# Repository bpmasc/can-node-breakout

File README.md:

# can-node-breakout

Version 0.0.1

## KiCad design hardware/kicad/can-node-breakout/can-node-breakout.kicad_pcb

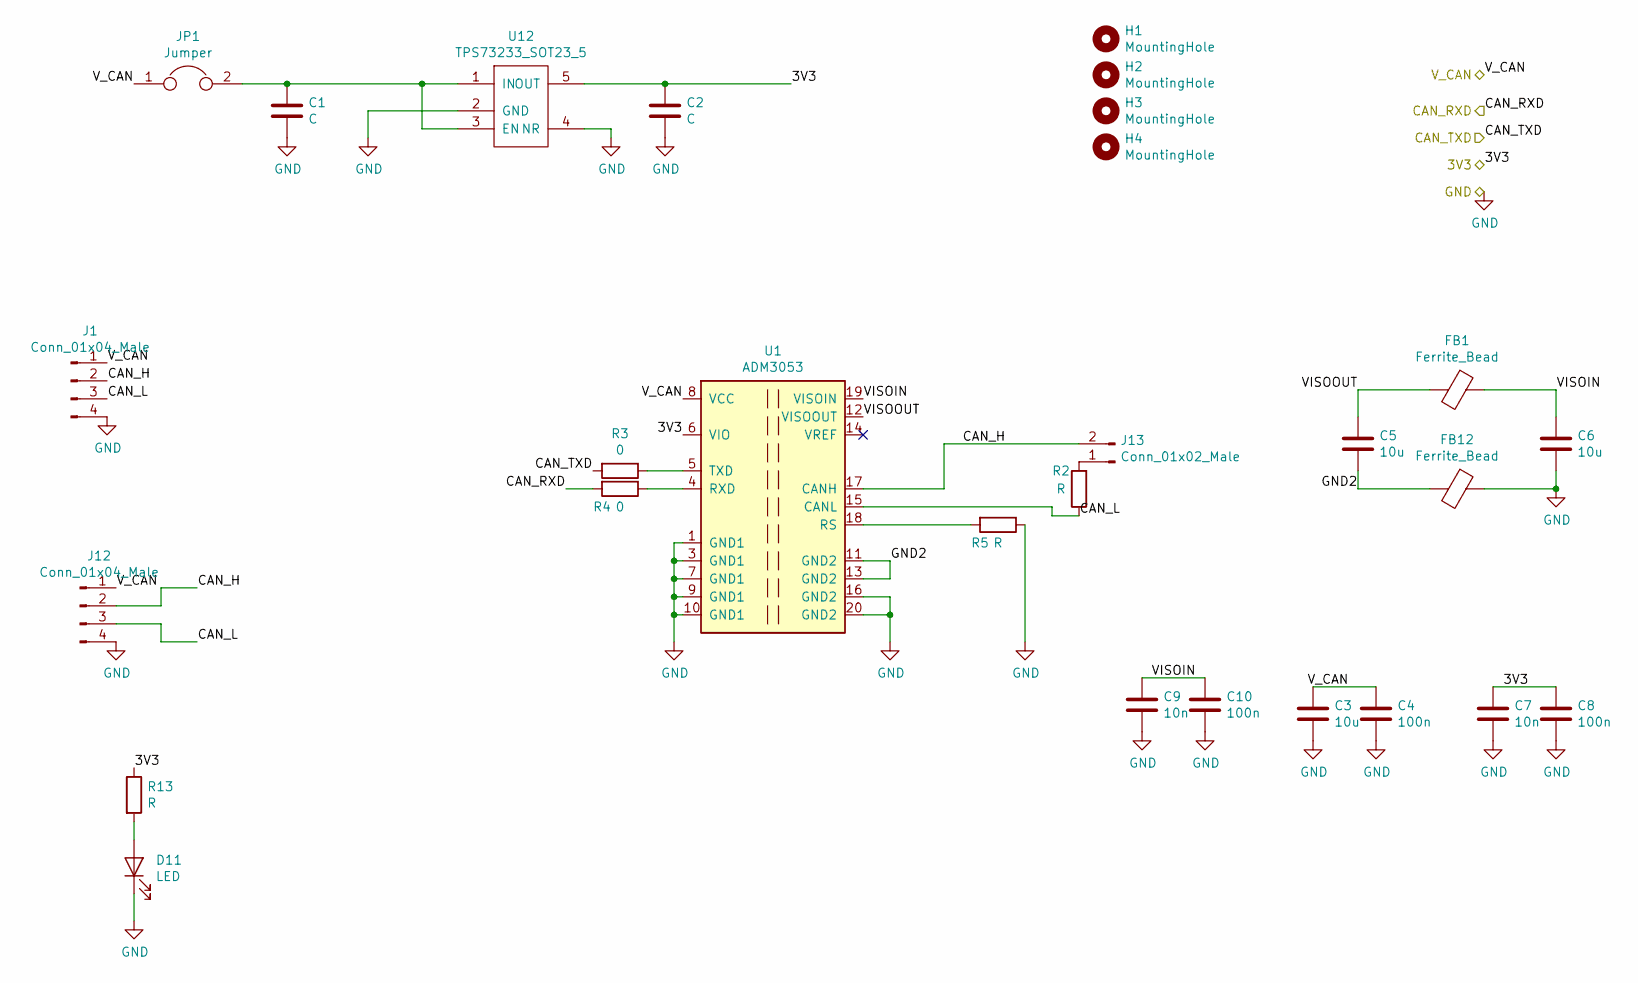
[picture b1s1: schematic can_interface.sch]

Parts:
C1, C2: C; C_0603
C3, C5, C6: 10u; C_0603
C4, C8, C10: 100n; C_0603
C7, C9: 10n; C_0603
D11: LED; LED_0603_1608Metric
FB1, FB12: Ferrite_Bead; L_0603
H1, H2, H3, H4: MountingHole; MountingHole_2.2mm_M2
J1, J12: Conn_01x04_Male; JST_GH_SM04B-GHS-TB_04x1.25mm_Angled
J13: Conn_01x02_Male; Pin_Header_Straight_1x02_Pitch2.54mm
JP1: Jumper; SolderJumper-2_P1.3mm_Open_Pad1.0x1.5mm
R2, R5, R13: R; R_0603_1608Metric
R3, R4: 0; R_0603_1608Metric
U1: ADM3053; SOIC-20W_7.5x12.8mm_Pitch1.27mm
U12: TPS73233_SOT23_5; SOT-23-5

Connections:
/can_interface/3V3: C2.1, C7.1, C8.1, R13.1, U1.6 (VIO), U12.5 (OUT); also elsewhere on the board
/can_interface/CAN_H: J1.2, J12.2, J13.2, U1.17 (CANH)
/can_interface/CAN_L: J1.3, J12.3, R2.1, U1.15 (CANL)
/can_interface/CAN_RXD: R4.2; also elsewhere on the board
/can_interface/CAN_TXD: R3.2; also elsewhere on the board
/can_interface/GND2: C5.2, FB12.2, U1.11 (GND2), U1.13 (GND2)
/can_interface/VISOIN: C6.1, C9.1, C10.1, FB1.1, U1.19 (VISOIN)
/can_interface/VISOOUT: C5.1, FB1.2, U1.12 (VISOOUT)
/can_interface/V_CAN: C3.1, C4.1, J1.1, J12.1, JP1.1, U1.8 (VCC); also elsewhere on the board
GND: C1.2, C2.2, C3.2, C4.2, C6.2, C7.2, C8.2, C9.2, C10.2, D11.1 (K), FB12.1, J1.4, J12.4, R5.1, U1.1 (GND1), U1.3 (GND1), U1.7 (GND1), U1.9 (GND1), U1.10 (GND1), U1.16 (GND2), U1.20 (GND2), U12.2 (GND), U12.4 (NR); also elsewhere on the board
unnamed: C1.1, JP1.2, U12.1 (IN), U12.3 (EN)
unnamed: D11.2 (A), R13.2
unnamed: J13.1, R2.2
unnamed: R3.1, U1.5 (TXD)
unnamed: R4.1, U1.4 (RXD)
unnamed: R5.2, U1.18 (RS)

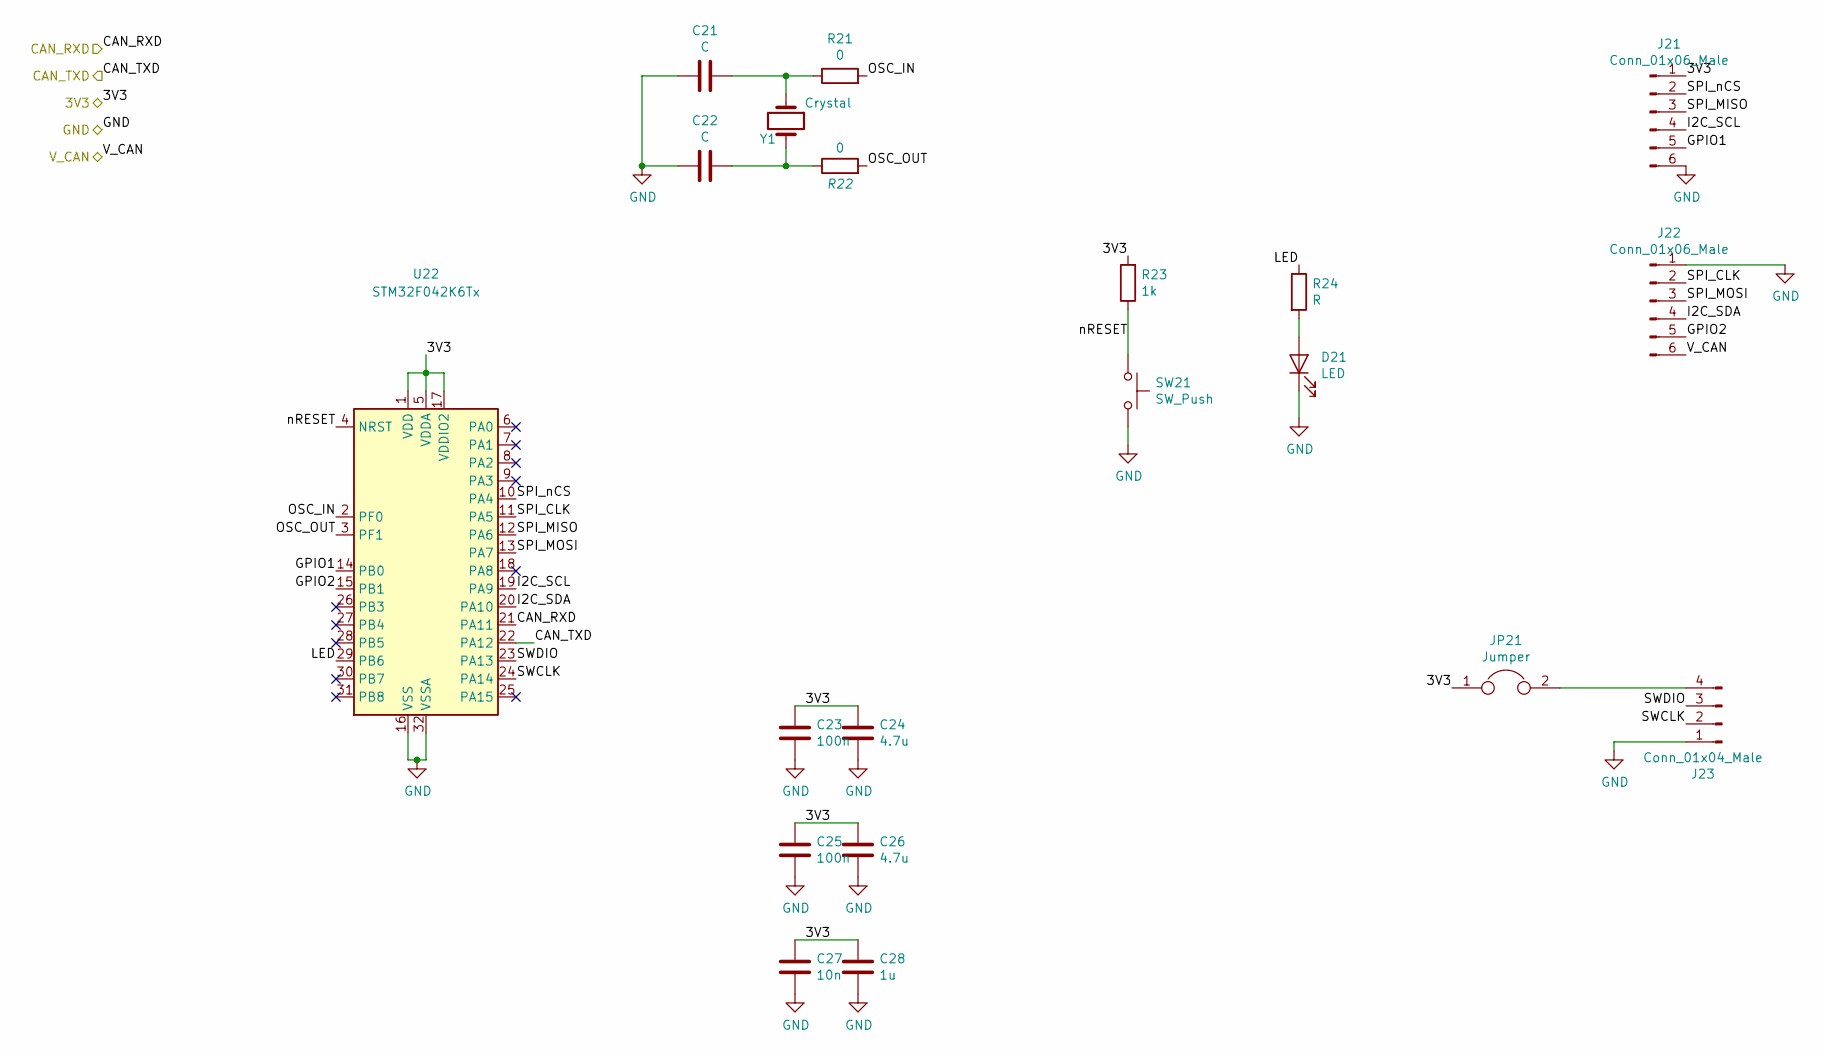
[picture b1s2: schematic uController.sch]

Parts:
C21, C22: C; C_0603
C23, C25: 100n; C_0603
C24, C26: 4.7u; C_0603
C27: 10n; C_0603
C28: 1u; C_0603
D21: LED; LED_0603_1608Metric
J21, J22: Conn_01x06_Male; Pin_Header_Straight_1x06_Pitch2.54mm
J23: Conn_01x04_Male; Pin_Header_Straight_1x04_Pitch2.54mm
JP21: Jumper; SolderJumper-2_P1.3mm_Open_Pad1.0x1.5mm
R21, R22: 0; R_0603_1608Metric
R23: 1k; R_0603_1608Metric
R24: R; R_0603_1608Metric
SW21: SW_Push; Switch_Tactile_SMD_4.5x4.5mm_TL3315NF160Q
U22: STM32F042K6Tx; LQFP-32_7x7mm_Pitch0.8mm
Y1: Crystal; Crystal_SMD_0603-2pin_6.0x3.5mm

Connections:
/can_interface/3V3: C23.1, C24.1, C25.1, C26.1, C27.1, C28.1, J21.1, JP21.1, R23.2, U22.1 (VDD), U22.5 (VDDA), U22.17 (VDDIO2); also elsewhere on the board
/can_interface/CAN_RXD: U22.21 (PA11); also elsewhere on the board
/can_interface/CAN_TXD: U22.22 (PA12); also elsewhere on the board
/can_interface/V_CAN: J22.6; also elsewhere on the board
/uController/GPIO1: J21.5, U22.14 (PB0)
/uController/GPIO2: J22.5, U22.15 (PB1)
/uController/I2C_SCL: J21.4, U22.19 (PA9)
/uController/I2C_SDA: J22.4, U22.20 (PA10)
/uController/LED: R24.1, U22.29 (PB6)
/uController/OSC_IN: R21.2, U22.2 (PF0)
/uController/OSC_OUT: R22.2, U22.3 (PF1)
/uController/SPI_CLK: J22.2, U22.11 (PA5)
/uController/SPI_MISO: J21.3, U22.12 (PA6)
/uController/SPI_MOSI: J22.3, U22.13 (PA7)
/uController/SPI_nCS: J21.2, U22.10 (PA4)
/uController/SWCLK: J23.2, U22.24 (PA14)
/uController/SWDIO: J23.3, U22.23 (PA13)
/uController/nRESET: R23.1, SW21.1, U22.4 (NRST)
GND: C21.2, C22.2, C23.2, C24.2, C25.2, C26.2, C27.2, C28.2, D21.1 (K), J21.6, J22.1, J23.1, SW21.2, U22.16 (VSS), U22.32 (VSSA); also elsewhere on the board
unnamed: C21.1, R21.1, Y1.1
unnamed: C22.1, R22.1, Y1.2
unnamed: D21.2 (A), R24.2
unnamed: J23.4, JP21.2

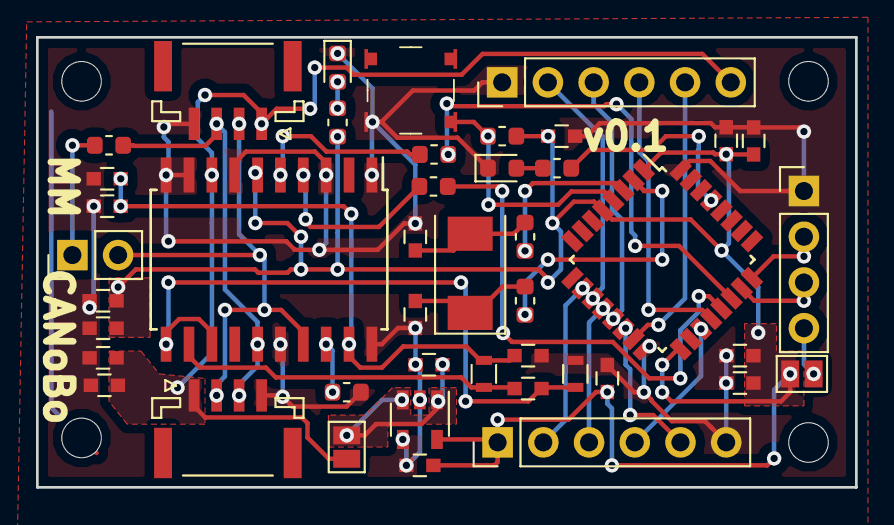
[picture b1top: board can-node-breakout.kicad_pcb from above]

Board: 2 copper layers, 45.5 x 25.0 mm, 48 parts (0 on the bottom side), 34 nets.

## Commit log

2019-04-05 Added hardware rev.1
2019-04-05 Added rev. 2.
